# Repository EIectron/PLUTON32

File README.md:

# PLUTON32
An open source **Raspberry Pi Zero** size ESP32 development board

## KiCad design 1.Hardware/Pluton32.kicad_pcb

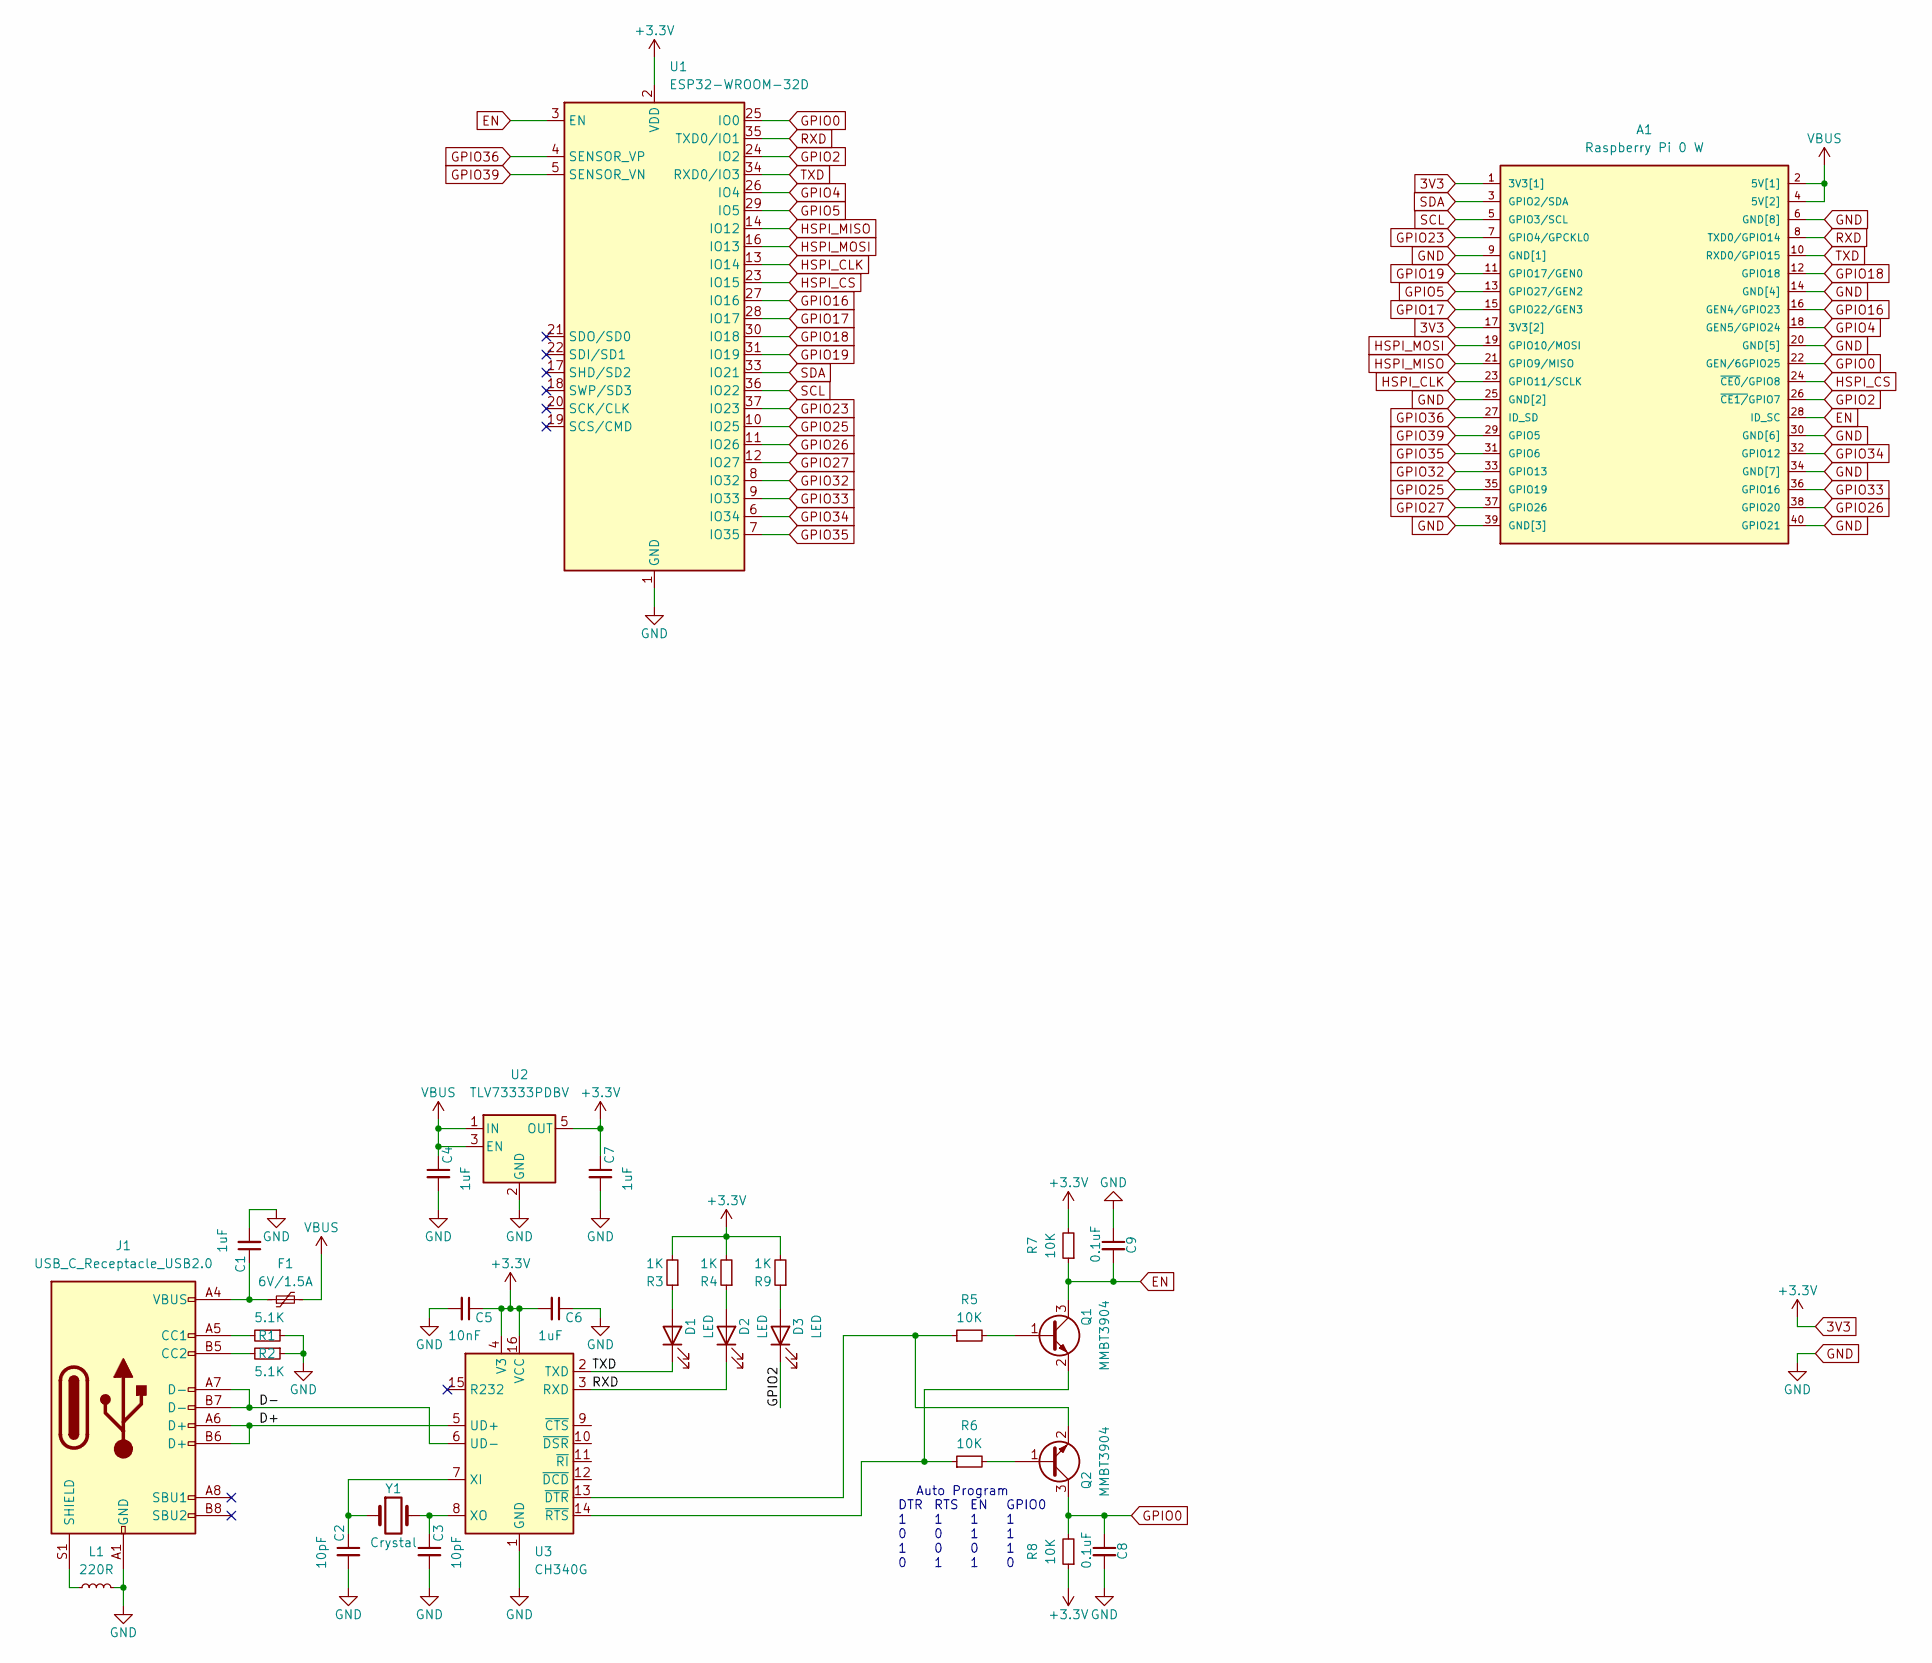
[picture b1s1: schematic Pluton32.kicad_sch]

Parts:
A1: Raspberry Pi 0 W; RP0-Board
C1, C4, C6, C7: 1uF; C_0603_1608Metric
C2, C3: 10pF; C_0603_1608Metric
C5: 10nF; C_0603_1608Metric
C8, C9: 0.1uF; C_0603_1608Metric
D1, D2, D3: LED; LED_0805_2012Metric
F1: 6V/1.5A; Fuse_0805_2012Metric
J1: USB_C_Receptacle_USB2.0; USB_C_Receptacle_HRO_TYPE-C-31-M-12; Manufacturer Part Number TYPE-C-31-M-12
L1: 220R; L_0603_1608Metric
Q1, Q2: MMBT3904; SOT-23
R1, R2: 5.1K; R_0603_1608Metric
R3, R4, R9: 1K; R_0603_1608Metric
R5, R6, R7, R8: 10K; R_0603_1608Metric
U1: ESP32-WROOM-32D; ESP32-WROOM-32
U2: TLV73333PDBV; SOT-23-5
U3: CH340G; SOIC-16_3.9x9.9mm_P1.27mm
Y1: Crystal; Crystal_SMD_HC49-SD

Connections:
3V3: A1.1 (3V3[1]), A1.17 (3V3[2]), C5.1, C6.2, C7.1, R3.2, R4.2, R7.2, R8.1, R9.2, U1.2 (VDD), U2.5 (OUT), U3.4 (V3), U3.16 (VCC)
/D+: J1.A6 (D+), J1.B6 (D+), U3.5 (UD+)
/D-: J1.A7 (D-), J1.B7 (D-), U3.6 (UD-)
EN: A1.28 (ID_SC), C9.2, Q1.3 (C), R7.1, U1.3 (EN)
GND: A1.6 (GND[8]), A1.9 (GND[1]), A1.14 (GND[4]), A1.20 (GND[5]), A1.25 (GND[2]), A1.30 (GND[6]), A1.34 (GND[7]), A1.39 (GND[3]), A1.40 (GPIO21), C1.2, C2.2, C3.2, C4.2, C5.2, C6.1, C7.2, C8.2, C9.1, J1.A1 (GND), J1.A12 (GND), J1.B1 (GND), J1.B12 (GND), L1.2, R1.1, R2.1, U1.1 (GND), U1.15 (GND), U1.38 (GND), U1.39 (GND), U2.2 (GND), U3.1 (GND)
GPIO0: A1.22 (GEN/6GPIO25), C8.1, Q2.3 (C), R8.2, U1.25 (IO0)
GPIO2: A1.26 (~CE1/GPIO7), D3.1 (K), U1.24 (IO2)
GPIO4: A1.18 (GEN5/GPIO24), U1.26 (IO4)
GPIO5: A1.13 (GPIO27/GEN2), U1.29 (IO5)
GPIO16: A1.16 (GEN4/GPIO23), U1.27 (IO16)
GPIO17: A1.15 (GPIO22/GEN3), U1.28 (IO17)
GPIO18: A1.12 (GPIO18), U1.30 (IO18)
GPIO19: A1.11 (GPIO17/GEN0), U1.31 (IO19)
GPIO23: A1.7 (GPIO4/GPCKL0), U1.37 (IO23)
GPIO25: A1.35 (GPIO19), U1.10 (IO25)
GPIO26: A1.38 (GPIO20), U1.11 (IO26)
GPIO27: A1.37 (GPIO26), U1.12 (IO27)
GPIO32: A1.33 (GPIO13), U1.8 (IO32)
GPIO33: A1.36 (GPIO16), U1.9 (IO33)
GPIO34: A1.32 (GPIO12), U1.6 (IO34)
GPIO35: A1.31 (GPIO6), U1.7 (IO35)
GPIO36: A1.27 (ID_SD), U1.4 (SENSOR_VP)
GPIO39: A1.29 (GPIO5), U1.5 (SENSOR_VN)
HSPI_CLK: A1.23 (GPIO11/SCLK), U1.13 (IO14)
HSPI_CS: A1.24 (~CE0/GPIO8), U1.23 (IO15)
HSPI_MISO: A1.21 (GPIO9/MISO), U1.14 (IO12)
HSPI_MOSI: A1.19 (GPIO10/MOSI), U1.16 (IO13)
unnamed: C1.1, F1.1, J1.A4 (VBUS), J1.A9 (VBUS), J1.B4 (VBUS), J1.B9 (VBUS)
unnamed: C2.1, U3.7 (XI), Y1.1
unnamed: C3.1, U3.8 (XO), Y1.2
unnamed: D1.2 (A), R3.1
unnamed: D2.2 (A), R4.1
unnamed: D3.2 (A), R9.1
unnamed: J1.A5 (CC1), R1.2
unnamed: J1.B5 (CC2), R2.2
unnamed: J1.S1 (SHIELD), L1.1
unnamed: Q1.1 (B), R5.2
unnamed: Q1.2 (E), R6.1, U3.14 (~RTS)
unnamed: Q2.1 (B), R6.2
unnamed: Q2.2 (E), R5.1, U3.13 (~DTR)
RXD: A1.8 (TXD0/GPIO14), D2.1 (K), U1.35 (TXD0/IO1), U3.3 (RXD)
SCL: A1.5 (GPIO3/SCL), U1.36 (IO22)
SDA: A1.3 (GPIO2/SDA), U1.33 (IO21)
TXD: A1.10 (RXD0/GPIO15), D1.1 (K), U1.34 (RXD0/IO3), U3.2 (TXD)
VBUS: A1.2 (5V[1]), A1.4 (5V[2]), C4.1, F1.2, U2.1 (IN), U2.3 (EN)

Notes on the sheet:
RTS 1 0 0 1
GPIO0 1 1 1 0
Auto Program
EN 1 1 0 1
DTR 1 0 1 0

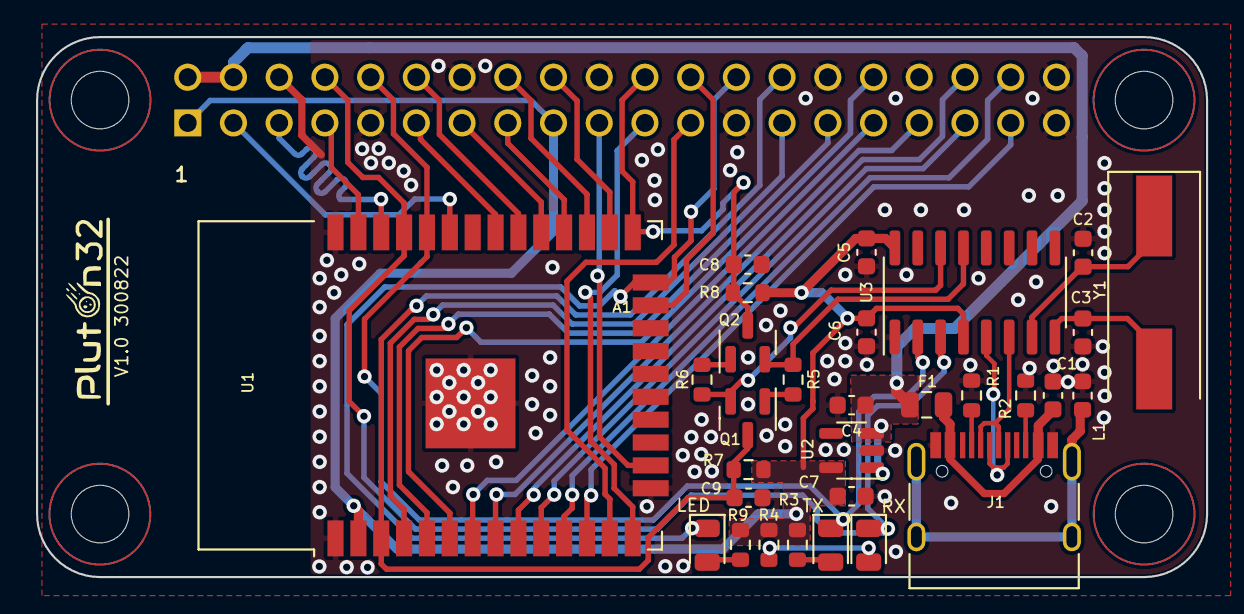
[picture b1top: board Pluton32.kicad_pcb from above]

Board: 2 copper layers, 65.0 x 30.0 mm, 31 parts (0 on the bottom side), 45 nets.

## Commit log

2022-09-02 Upload first files
2022-09-03 UPDATE IMAGES
2023-11-20 add schematic pdf
